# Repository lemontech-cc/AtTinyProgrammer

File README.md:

# AtTinyPtogrammer

AtTiny Programmer is not a simple shield for arduino one but it is a complete PCB that uses a Pro Micro card to directly program the AtTiny family processors.

You can program Attiny84 and Attiny85 with a simple USB cable and the Arduino IDE.

### Instruction of Use:

Use the Dip8 socket to Proram [AtTiny85](https://www.microchip.com/wwwproducts/en/ATtiny85) and each other processors with this socket of AVR Attiny family:

* AtTiny25
* AtTiny45
* AtTiny85

Use the Dip14 socket to Proram [AtTiny84](https://www.microchip.com/wwwproducts/en/ATtiny84) and each other processors with this socket of AVR Attiny family:

* AtTiny24
* AtTiny44
* AtTiny84

### To pre-programming the Pro Micro

** Step 1 **

Remove the jumper J1 and select on the Arduino IDE the sketch 
*Examples -> 11. ArduinoISO -> ArduinoISP*

Select the board: *Arduino Pro or Pro Mini*

Upload the sketch on the Pro Micro ...

** Step 2 **
Reconnect the jumper J1 and select in the Arduino IDE the Attiny processor family, es: Attiny85;

In teh Tools menu select:

*Programmer: Arduino as ISP*

** Step 3 **

Select your sketch for Attiny85 and Upload it.

More Info: [lemontech.cc](http://www.lemontech.cc)

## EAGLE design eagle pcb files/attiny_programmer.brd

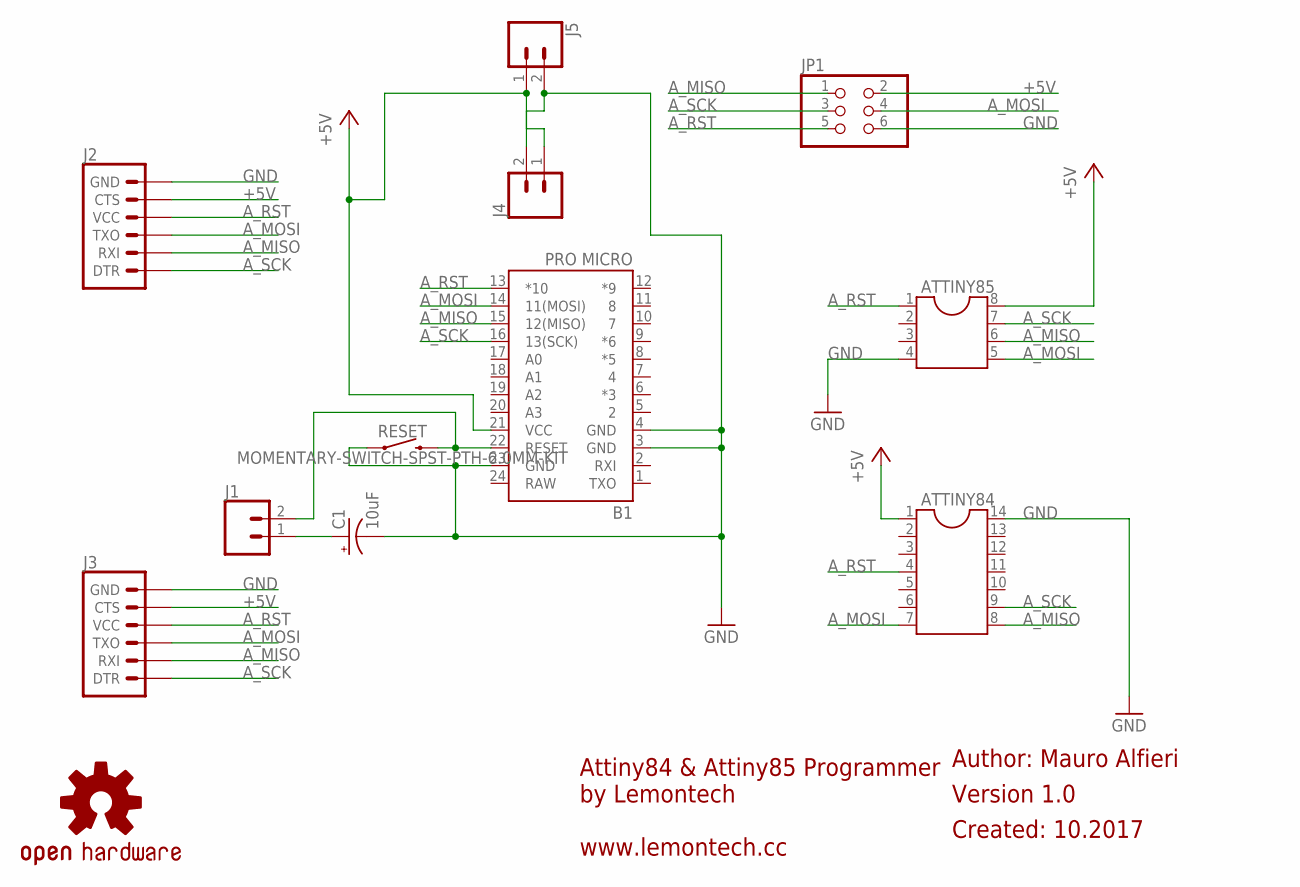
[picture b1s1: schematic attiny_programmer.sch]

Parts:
ATTINY84: DIL14S; SOCKET-14
ATTINY85: DIL8S; SOCKET-08
B1: PRO MICRO; SPARKFUN_PRO_MICRO
C1: 10uF; CPOL-RADIAL-2.5MM-5MM
J1, J4, J5: CONN_02; 1X02
J2, J3: 6_PIN_SERIAL_TARGETLONGPADS; 1X06_LONGPADS
JP1: PINHD-2X3; 2X03
LOGO1: OSHW-LOGOMINI; OSHW-LOGO-MINI
RESET: MOMENTARY-SWITCH-SPST-PTH-6.0MM-KIT; TACTILE_SWITCH_PTH_6.0MM_KIT

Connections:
+5V: ATTINY84.1, ATTINY85.8, B1.21 (VCC), J2.5 (CTS), J3.5 (CTS), J4.1, J5.1, JP1.2
A_MISO: ATTINY84.8, ATTINY85.6, B1.15 (12(MISO)), J2.2 (RXI), J3.2 (RXI), JP1.1
A_MOSI: ATTINY84.7, ATTINY85.5, B1.14 (11(MOSI)), J2.3 (TXO), J3.3 (TXO), JP1.4
A_RST: ATTINY84.4, ATTINY85.1, B1.13 (*10), J2.4 (VCC), J3.4 (VCC), JP1.5
A_SCK: ATTINY84.9, ATTINY85.7, B1.16 (13(SCK)), J2.1 (DTR), J3.1 (DTR), JP1.3
GND: ATTINY84.14, ATTINY85.4, B1.3 (GND), B1.4 (GND), B1.23 (GND), C1.2 (-), J2.6 (GND), J3.6 (GND), J4.2, J5.2, JP1.6, RESET.1
unnamed: B1.22 (RESET), J1.2, RESET.3 (2)
unnamed: C1.1 (+), J1.1
RAW: B1.24 (RAW)

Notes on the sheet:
Attiny84 & Attiny85 Programmer by Lemontech www.lemontech.cc
Version 1.0
Author: Mauro Alfieri
Created: 10.2017

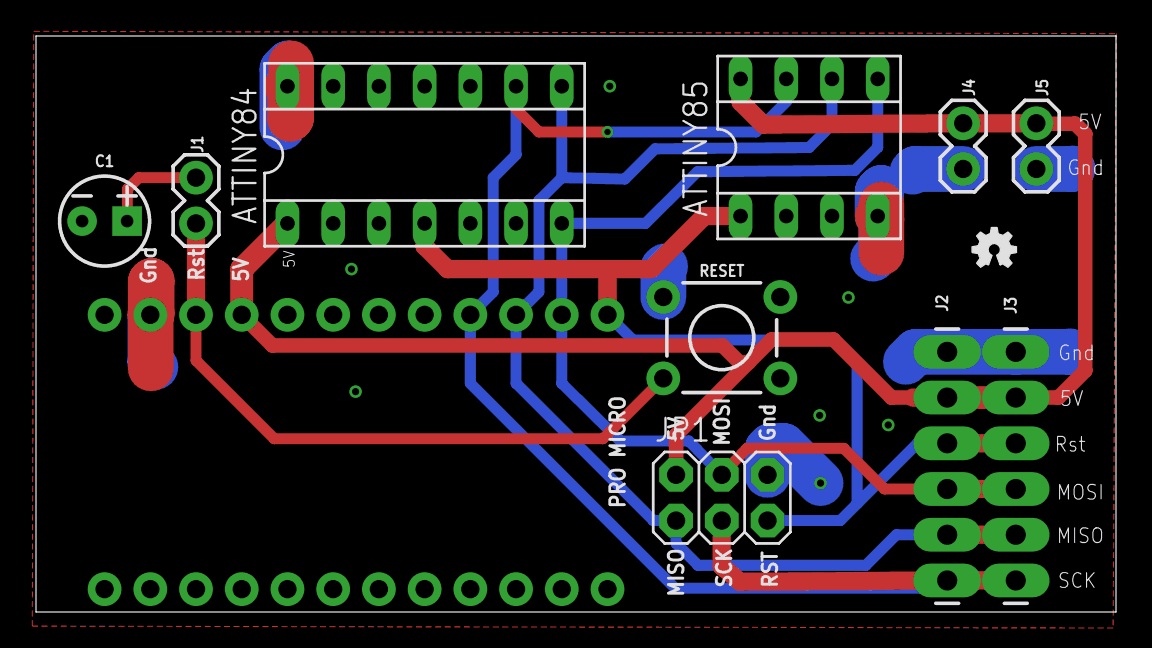
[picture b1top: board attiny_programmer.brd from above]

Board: 2 copper layers, 60.0 x 32.0 mm, 13 parts (1 on the bottom side), 8 nets.

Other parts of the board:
U$1: LOGO_1MIL

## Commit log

2018-08-18 Added PCBs files and imaged of product assembled
2018-08-18 Added two images

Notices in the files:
parts and their libraries:
SparkFun-Boards: Licensing: Creative Commons ShareAlike 4.0 International - https://creativecommons.org/licenses/by-sa/4.0
